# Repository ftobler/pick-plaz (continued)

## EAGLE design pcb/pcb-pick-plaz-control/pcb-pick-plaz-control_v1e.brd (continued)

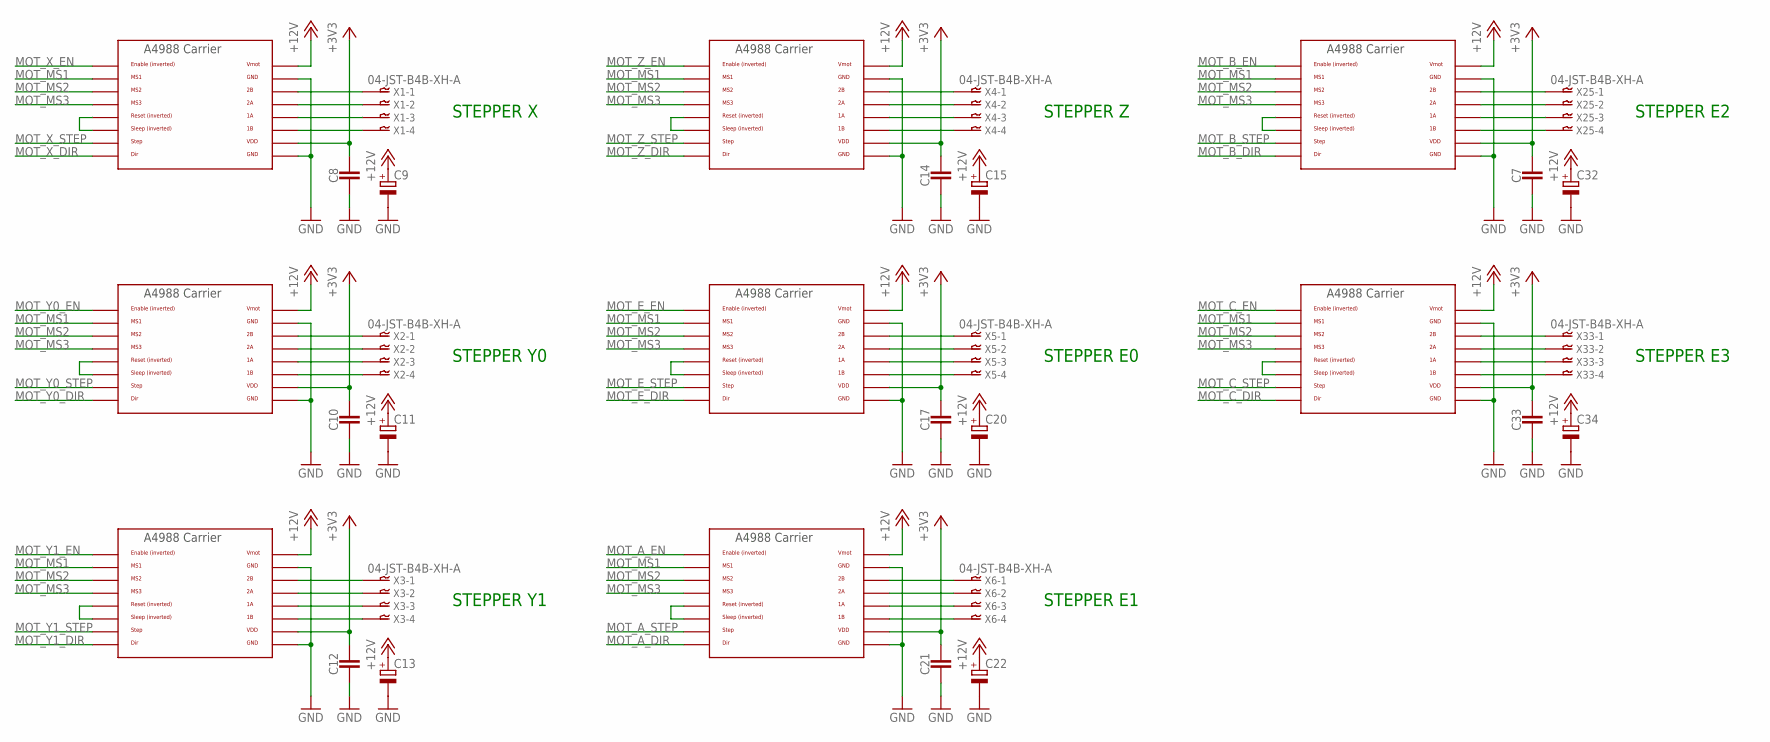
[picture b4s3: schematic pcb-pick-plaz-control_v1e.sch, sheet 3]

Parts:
C7, C8, C10, C12, C14, C17, C21, C33: CAPACITOR0603_CAP; 0603_CAP
C9, C11, C13, C15, C20, C22, C32, C34: CPOL-EU175TMP-0808; 175TMP-0808
U$2, U$3, U$4, U$5, U$6, U$7, U$8, U$9: A4988BREAKOUT
X1, X2, X3, X4, X5, X6, X25, X33: 04-JST-B4B-XH-A; B4B-XH

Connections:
+3V3: C7.1, C8.1, C10.1, C12.1, C14.1, C17.1, C21.1, C33.1, U$2.VDD, U$3.VDD, U$4.VDD, U$5.VDD, U$6.VDD, U$7.VDD, U$8.VDD, U$9.VDD; also elsewhere on the board
+12V: C9.+, C11.+, C13.+, C15.+, C20.+, C22.+, C32.+, C34.+, U$2.VMOT, U$3.VMOT, U$4.VMOT, U$5.VMOT, U$6.VMOT, U$7.VMOT, U$8.VMOT, U$9.VMOT; also elsewhere on the board
GND: C7.2, C8.2, C9.-, C10.2, C11.-, C12.2, C13.-, C14.2, C15.-, C17.2, C20.-, C21.2, C22.-, C32.-, C33.2, C34.-, U$2.GND, U$2.GND@0 (GND), U$3.GND, U$3.GND@0 (GND), U$4.GND, U$4.GND@0 (GND), U$5.GND, U$5.GND@0 (GND), U$6.GND, U$6.GND@0 (GND), U$7.GND, U$7.GND@0 (GND), U$8.GND, U$8.GND@0 (GND), U$9.GND, U$9.GND@0 (GND); also elsewhere on the board
MOT_A_DIR: U$7.DIR; also elsewhere on the board
MOT_A_EN: U$7.EN; also elsewhere on the board
MOT_A_STEP: U$7.STEP; also elsewhere on the board
MOT_B_DIR: U$8.DIR; also elsewhere on the board
MOT_B_EN: U$8.EN; also elsewhere on the board
MOT_B_STEP: U$8.STEP; also elsewhere on the board
MOT_C_DIR: U$9.DIR; also elsewhere on the board
MOT_C_EN: U$9.EN; also elsewhere on the board
MOT_C_STEP: U$9.STEP; also elsewhere on the board
MOT_E_DIR: U$6.DIR; also elsewhere on the board
MOT_E_EN: U$6.EN; also elsewhere on the board
MOT_E_STEP: U$6.STEP; also elsewhere on the board
MOT_MS1: U$2.MS1, U$3.MS1, U$4.MS1, U$5.MS1, U$6.MS1, U$7.MS1, U$8.MS1, U$9.MS1; also elsewhere on the board
MOT_MS2: U$2.MS2, U$3.MS2, U$4.MS2, U$5.MS2, U$6.MS2, U$7.MS2, U$8.MS2, U$9.MS2; also elsewhere on the board
MOT_MS3: U$2.MS3, U$3.MS3, U$4.MS3, U$5.MS3, U$6.MS3, U$7.MS3, U$8.MS3, U$9.MS3; also elsewhere on the board
MOT_X_DIR: U$2.DIR; also elsewhere on the board
MOT_X_EN: U$2.EN; also elsewhere on the board
MOT_X_STEP: U$2.STEP; also elsewhere on the board
MOT_Y0_DIR: U$3.DIR; also elsewhere on the board
MOT_Y0_EN: U$3.EN; also elsewhere on the board
MOT_Y0_STEP: U$3.STEP; also elsewhere on the board
MOT_Y1_DIR: U$4.DIR; also elsewhere on the board
MOT_Y1_EN: U$4.EN; also elsewhere on the board
MOT_Y1_STEP: U$4.STEP; also elsewhere on the board
MOT_Z_DIR: U$5.DIR; also elsewhere on the board
MOT_Z_EN: U$5.EN; also elsewhere on the board
MOT_Z_STEP: U$5.STEP; also elsewhere on the board
unnamed: U$2.2B, X1.P$1
unnamed: U$2.2A, X1.P$2
unnamed: U$2.1A, X1.P$3
unnamed: U$2.1B, X1.P$4
unnamed: U$6.2B, X5.P$1
unnamed: U$2.RST, U$2.SLP (SLEEP)
unnamed: U$6.2A, X5.P$2
unnamed: U$6.1A, X5.P$3
unnamed: U$3.2B, X2.P$1
unnamed: U$3.2A, X2.P$2
unnamed: U$3.1A, X2.P$3
unnamed: U$3.1B, X2.P$4
unnamed: U$3.RST, U$3.SLP (SLEEP)
unnamed: U$4.2B, X3.P$1
unnamed: U$4.2A, X3.P$2
unnamed: U$4.1A, X3.P$3
unnamed: U$4.1B, X3.P$4
unnamed: U$4.RST, U$4.SLP (SLEEP)
unnamed: U$5.2B, X4.P$1
unnamed: U$5.2A, X4.P$2
unnamed: U$5.1A, X4.P$3
unnamed: U$5.1B, X4.P$4
unnamed: U$5.RST, U$5.SLP (SLEEP)
unnamed: U$6.1B, X5.P$4
unnamed: U$6.RST, U$6.SLP (SLEEP)
unnamed: U$7.2B, X6.P$1
unnamed: U$7.2A, X6.P$2
unnamed: U$7.1A, X6.P$3
unnamed: U$7.1B, X6.P$4
unnamed: U$7.RST, U$7.SLP (SLEEP)
unnamed: U$8.2B, X25.P$1
unnamed: U$8.2A, X25.P$2
unnamed: U$8.1A, X25.P$3
unnamed: U$8.1B, X25.P$4
unnamed: U$8.RST, U$8.SLP (SLEEP)
unnamed: U$9.2B, X33.P$1
unnamed: U$9.2A, X33.P$2
unnamed: U$9.1A, X33.P$3
unnamed: U$9.1B, X33.P$4
unnamed: U$9.RST, U$9.SLP (SLEEP)

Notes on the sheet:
STEPPER X
STEPPER Y0
STEPPER Y1
STEPPER Z
STEPPER E0
STEPPER E1
STEPPER E2
STEPPER E3

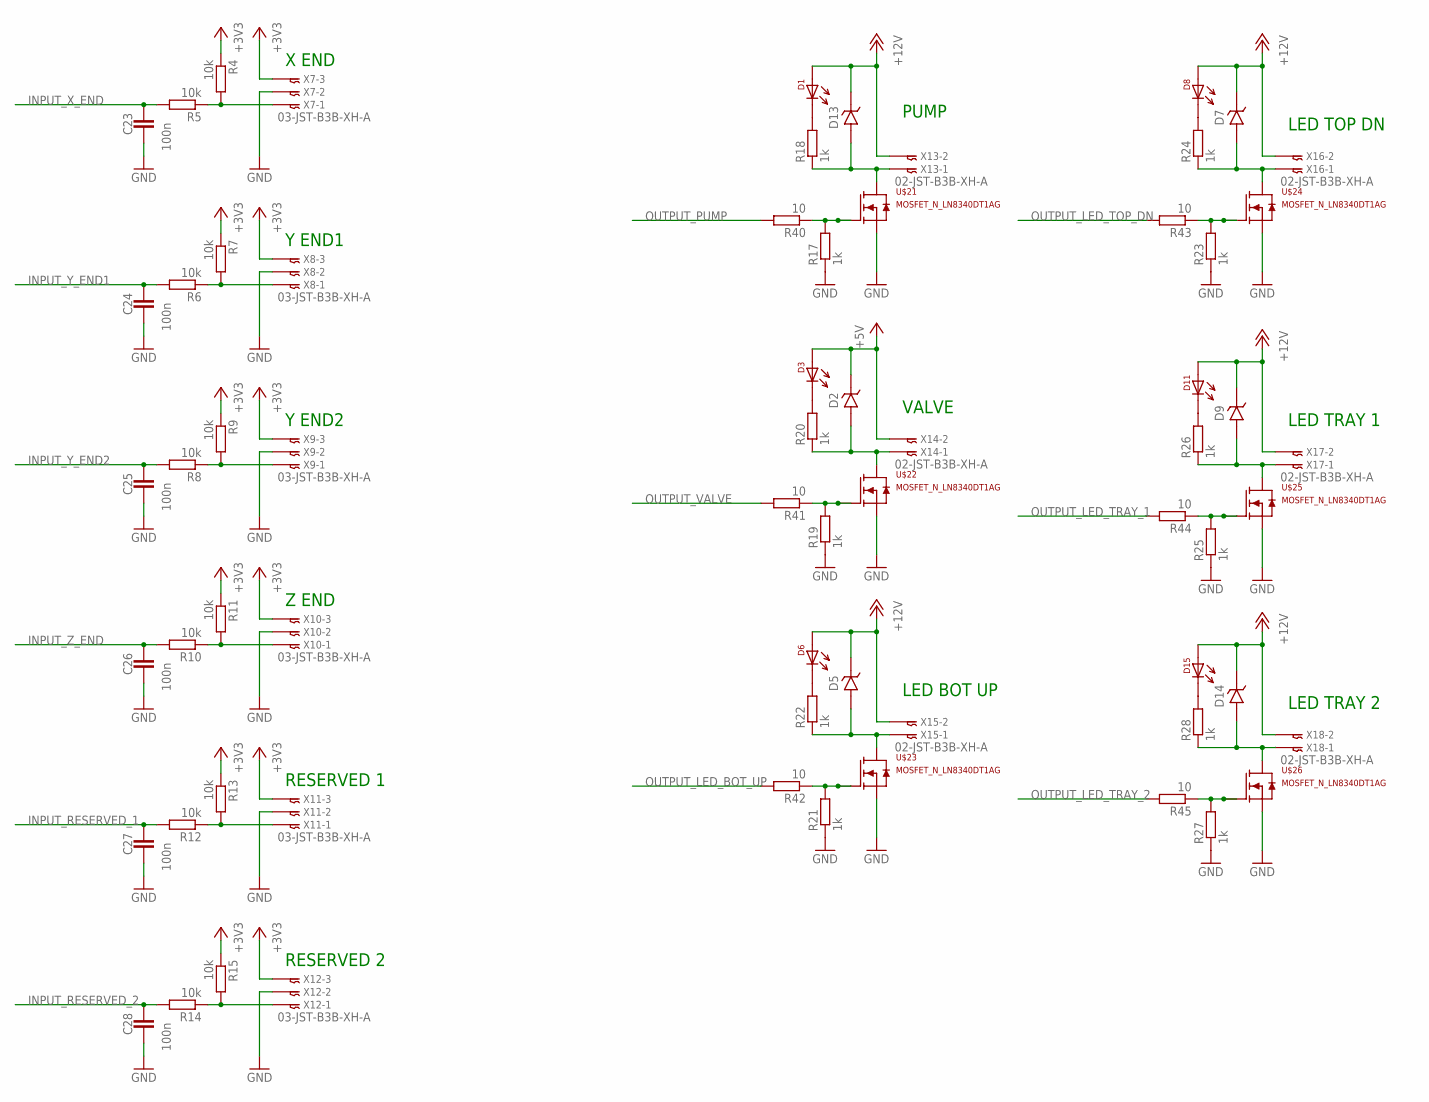
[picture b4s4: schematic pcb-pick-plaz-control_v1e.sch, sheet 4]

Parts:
C23, C24, C25, C26, C27, C28: 100n; 0603_CAP
D1, D3, D6, D8, D11, D15: LED-0805; 0805-DOT
D2, D5, D7, D9, D13, D14: DIODE_ZENERSOD123; SOD123
R4, R5, R6, R7, R8, R9, R10, R11, R12, R13, R14, R15: 10k; 0603-RES
R17, R18, R19, R20, R21, R22, R23, R24, R25, R26, R27, R28: 1k; 0603-RES
R40, R41, R42, R43, R44, R45: 10; 0603-RES
U$21, U$22, U$23, U$24, U$25, U$26: MOSFET_N_LN8340DT1AG; DFN3030-8B
X7, X8, X9, X10, X11, X12: 03-JST-B3B-XH-A; B3B-XH
X13, X14, X15, X16, X17, X18: 02-JST-B3B-XH-A; B2B-XH

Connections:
+3V3: R4.1, R7.1, R9.1, R11.1, R13.1, R15.1, X7.P$3, X8.P$3, X9.P$3, X10.P$3, X11.P$3, X12.P$3; also elsewhere on the board
+5V: D2.K (CATHODE), D3.1, X14.P$2; also elsewhere on the board
+12V: D1.1, D5.K (CATHODE), D6.1, D7.K (CATHODE), D8.1, D9.K (CATHODE), D11.1, D13.K (CATHODE), D14.K (CATHODE), D15.1, X13.P$2, X15.P$2, X16.P$2, X17.P$2, X18.P$2; also elsewhere on the board
GND: C23.2, C24.2, C25.2, C26.2, C27.2, C28.2, R17.1, R19.1, R21.1, R23.1, R25.1, R27.1, U$21.S1 (S), U$21.S2 (S), U$21.S3 (S), U$22.S1 (S), U$22.S2 (S), U$22.S3 (S), U$23.S1 (S), U$23.S2 (S), U$23.S3 (S), U$24.S1 (S), U$24.S2 (S), U$24.S3 (S), U$25.S1 (S), U$25.S2 (S), U$25.S3 (S), U$26.S1 (S), U$26.S2 (S), U$26.S3 (S), X7.P$2, X8.P$2, X9.P$2, X10.P$2, X11.P$2, X12.P$2; also elsewhere on the board
INPUT_RESERVED_1: C27.1, R12.2; also elsewhere on the board
INPUT_RESERVED_2: C28.1, R14.2; also elsewhere on the board
INPUT_X_END: C23.1, R5.2; also elsewhere on the board
INPUT_Y_END1: C24.1, R6.2; also elsewhere on the board
INPUT_Y_END2: C25.1, R8.2; also elsewhere on the board
INPUT_Z_END: C26.1, R10.2; also elsewhere on the board
unnamed: R4.2, R5.1, X7.P$1
unnamed: R6.1, R7.2, X8.P$1
unnamed: R8.1, R9.2, X9.P$1
unnamed: R10.1, R11.2, X10.P$1
unnamed: R12.1, R13.2, X11.P$1
unnamed: R14.1, R15.2, X12.P$1
unnamed: D13.A (ANODE), R18.1, U$21.D, X13.P$1
unnamed: R17.2, R40.1, U$21.G
unnamed: D1.2, R18.2
unnamed: D2.A (ANODE), R20.1, U$22.D, X14.P$1
unnamed: R19.2, R41.1, U$22.G
unnamed: D3.2, R20.2
unnamed: D5.A (ANODE), R22.1, U$23.D, X15.P$1
unnamed: R21.2, R42.1, U$23.G
unnamed: D6.2, R22.2
unnamed: D7.A (ANODE), R24.1, U$24.D, X16.P$1
unnamed: R23.2, R43.1, U$24.G
unnamed: D8.2, R24.2
unnamed: D9.A (ANODE), R26.1, U$25.D, X17.P$1
unnamed: R25.2, R44.1, U$25.G
unnamed: D11.2, R26.2
unnamed: D14.A (ANODE), R28.1, U$26.D, X18.P$1
unnamed: R27.2, R45.1, U$26.G
unnamed: D15.2, R28.2
OUTPUT_LED_BOT_UP: R42.2; also elsewhere on the board
OUTPUT_LED_TOP_DN: R43.2; also elsewhere on the board
OUTPUT_LED_TRAY_1: R44.2; also elsewhere on the board
OUTPUT_LED_TRAY_2: R45.2; also elsewhere on the board
OUTPUT_PUMP: R40.2; also elsewhere on the board
OUTPUT_VALVE: R41.2; also elsewhere on the board

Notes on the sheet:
PUMP
VALVE
LED BOT UP
LED TOP DN
LED TRAY 1
LED TRAY 2
X END
Y END1
Y END2
Z END
RESERVED 1
RESERVED 2

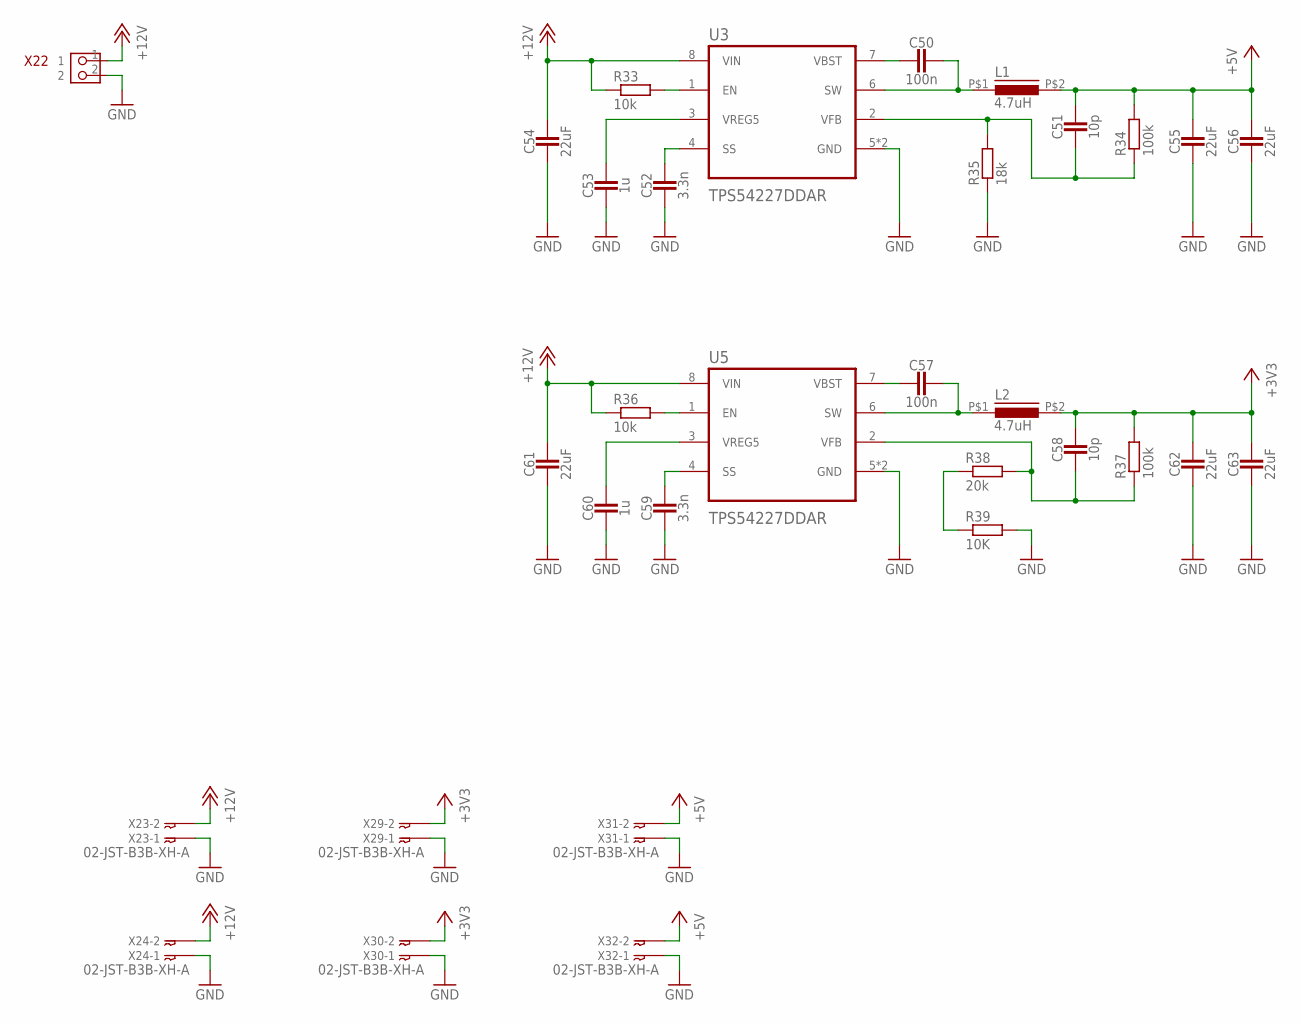
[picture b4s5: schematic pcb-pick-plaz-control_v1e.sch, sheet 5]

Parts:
C50, C57: 100n; 0603_CAP
C51, C58: 10p; 0603_CAP
C52, C59: 3.3n; 0603_CAP
C53, C60: 1u; 0603_CAP
C54, C61: 22uF; 1206_CAP
C55, C56, C62, C63: 22uF; 0805_CAP
L1, L2: 4.7uH; IND_CR4
R33, R36: 10k; 0603-RES
R34, R37: 100k; 0603-RES
R35: 18k; 0603-RES
R38: 20k; 0603-RES
R39: 10K; 0603-RES
U3, U5: TPS54227DDAR; TPS54227DDAR_VREG_LM5017MR/NOPB
X22: PIN_2X13.81MM_LONGPAD; PIN_2X1_3.81MM_LONGPAD
X23, X24, X29, X30, X31, X32: 02-JST-B3B-XH-A; B2B-XH

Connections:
+3V3: C58.1, C62.P$1 (1), C63.P$1 (1), L2.P$2 (2), R37.2, X29.P$2, X30.P$2; also elsewhere on the board
+5V: C51.1, C55.P$1 (1), C56.P$1 (1), L1.P$2 (2), R34.2, X31.P$2, X32.P$2; also elsewhere on the board
+12V: C54.1, C61.1, R33.1, R36.1, U3.8 (VIN), U5.8 (VIN), X22.1, X23.P$2, X24.P$2; also elsewhere on the board
GND: C52.2, C53.2, C54.2, C55.P$2 (2), C56.P$2 (2), C59.2, C60.2, C61.2, C62.P$2 (2), C63.P$2 (2), R35.1, R39.2, U3.5 (GND), U3.9 (GND), U5.5 (GND), U5.9 (GND), X22.2, X23.P$1, X24.P$1, X29.P$1, X30.P$1, X31.P$1, X32.P$1; also elsewhere on the board
unnamed: C50.2, U3.7 (VBST)
unnamed: C50.1, L1.P$1 (1), U3.6 (SW)
unnamed: C51.2, R34.1, R35.2, U3.2 (VFB)
unnamed: C52.1, U3.4 (SS)
unnamed: C53.1, U3.3 (VREG5)
unnamed: R33.2, U3.1 (EN)
unnamed: C57.2, U5.7 (VBST)
unnamed: C57.1, L2.P$1 (1), U5.6 (SW)
unnamed: C58.2, R37.1, R38.2, U5.2 (VFB)
unnamed: C59.1, U5.4 (SS)
unnamed: C60.1, U5.3 (VREG5)
unnamed: R36.2, U5.1 (EN)
unnamed: R38.1, R39.1

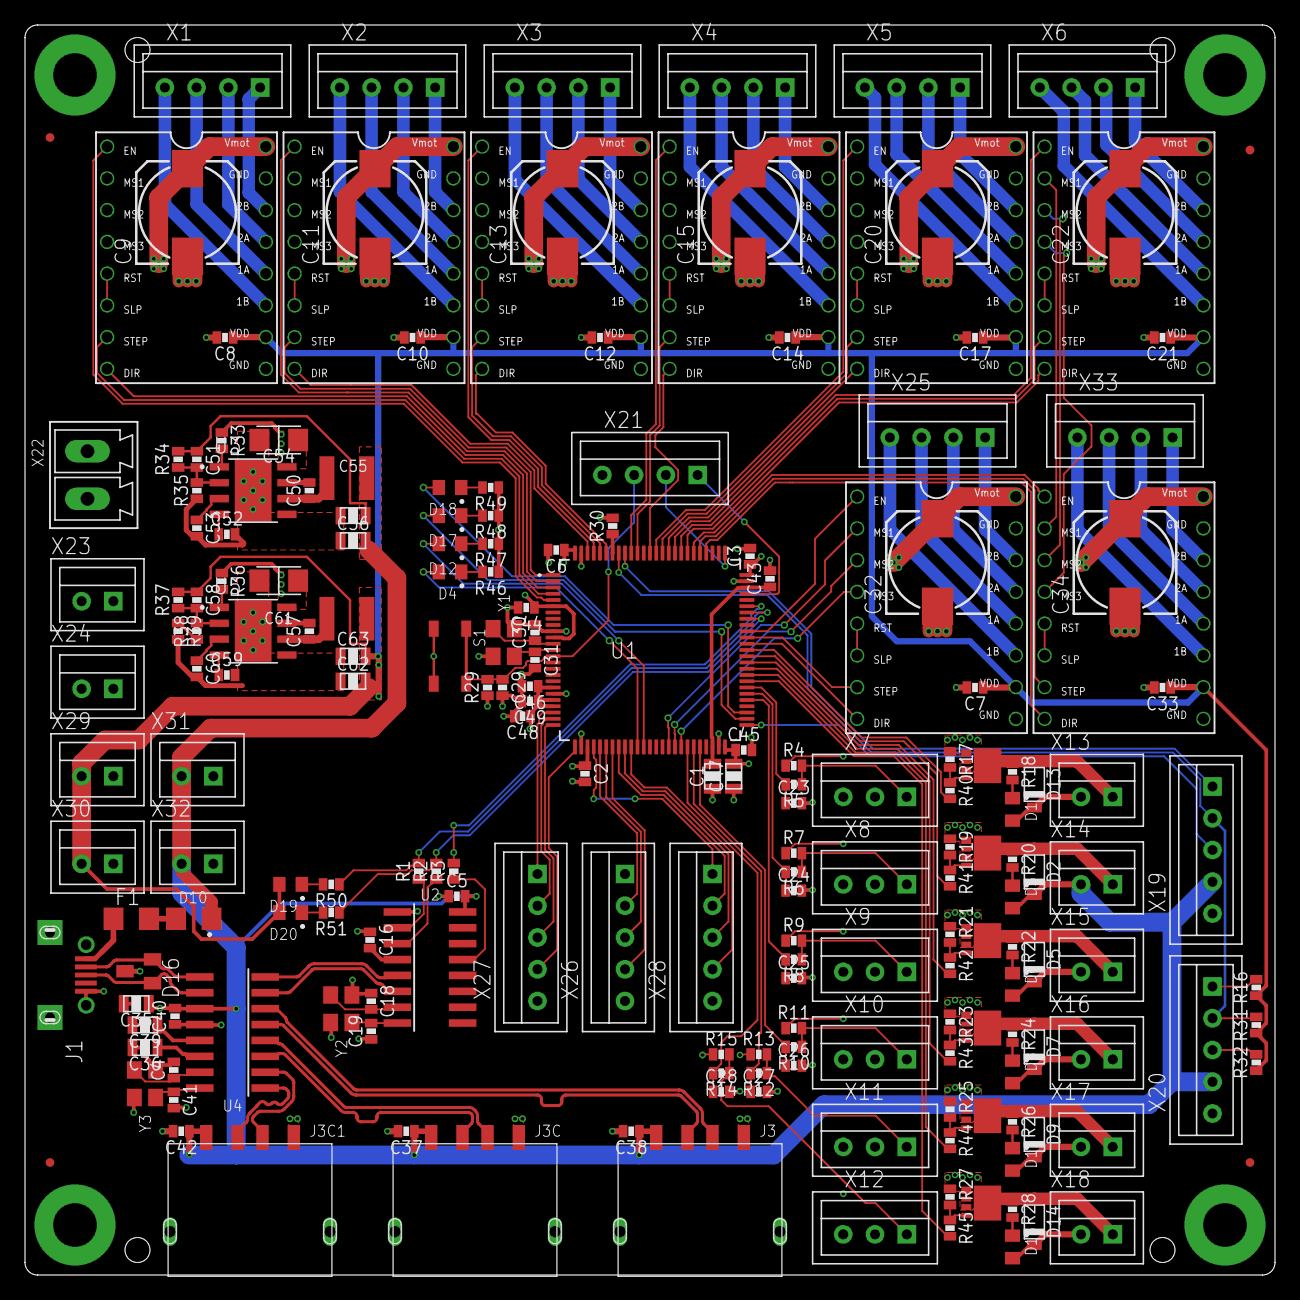
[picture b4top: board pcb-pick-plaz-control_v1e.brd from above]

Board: 4 copper layers, 100.0 x 100.0 mm, 202 parts (0 on the bottom side), 176 nets.

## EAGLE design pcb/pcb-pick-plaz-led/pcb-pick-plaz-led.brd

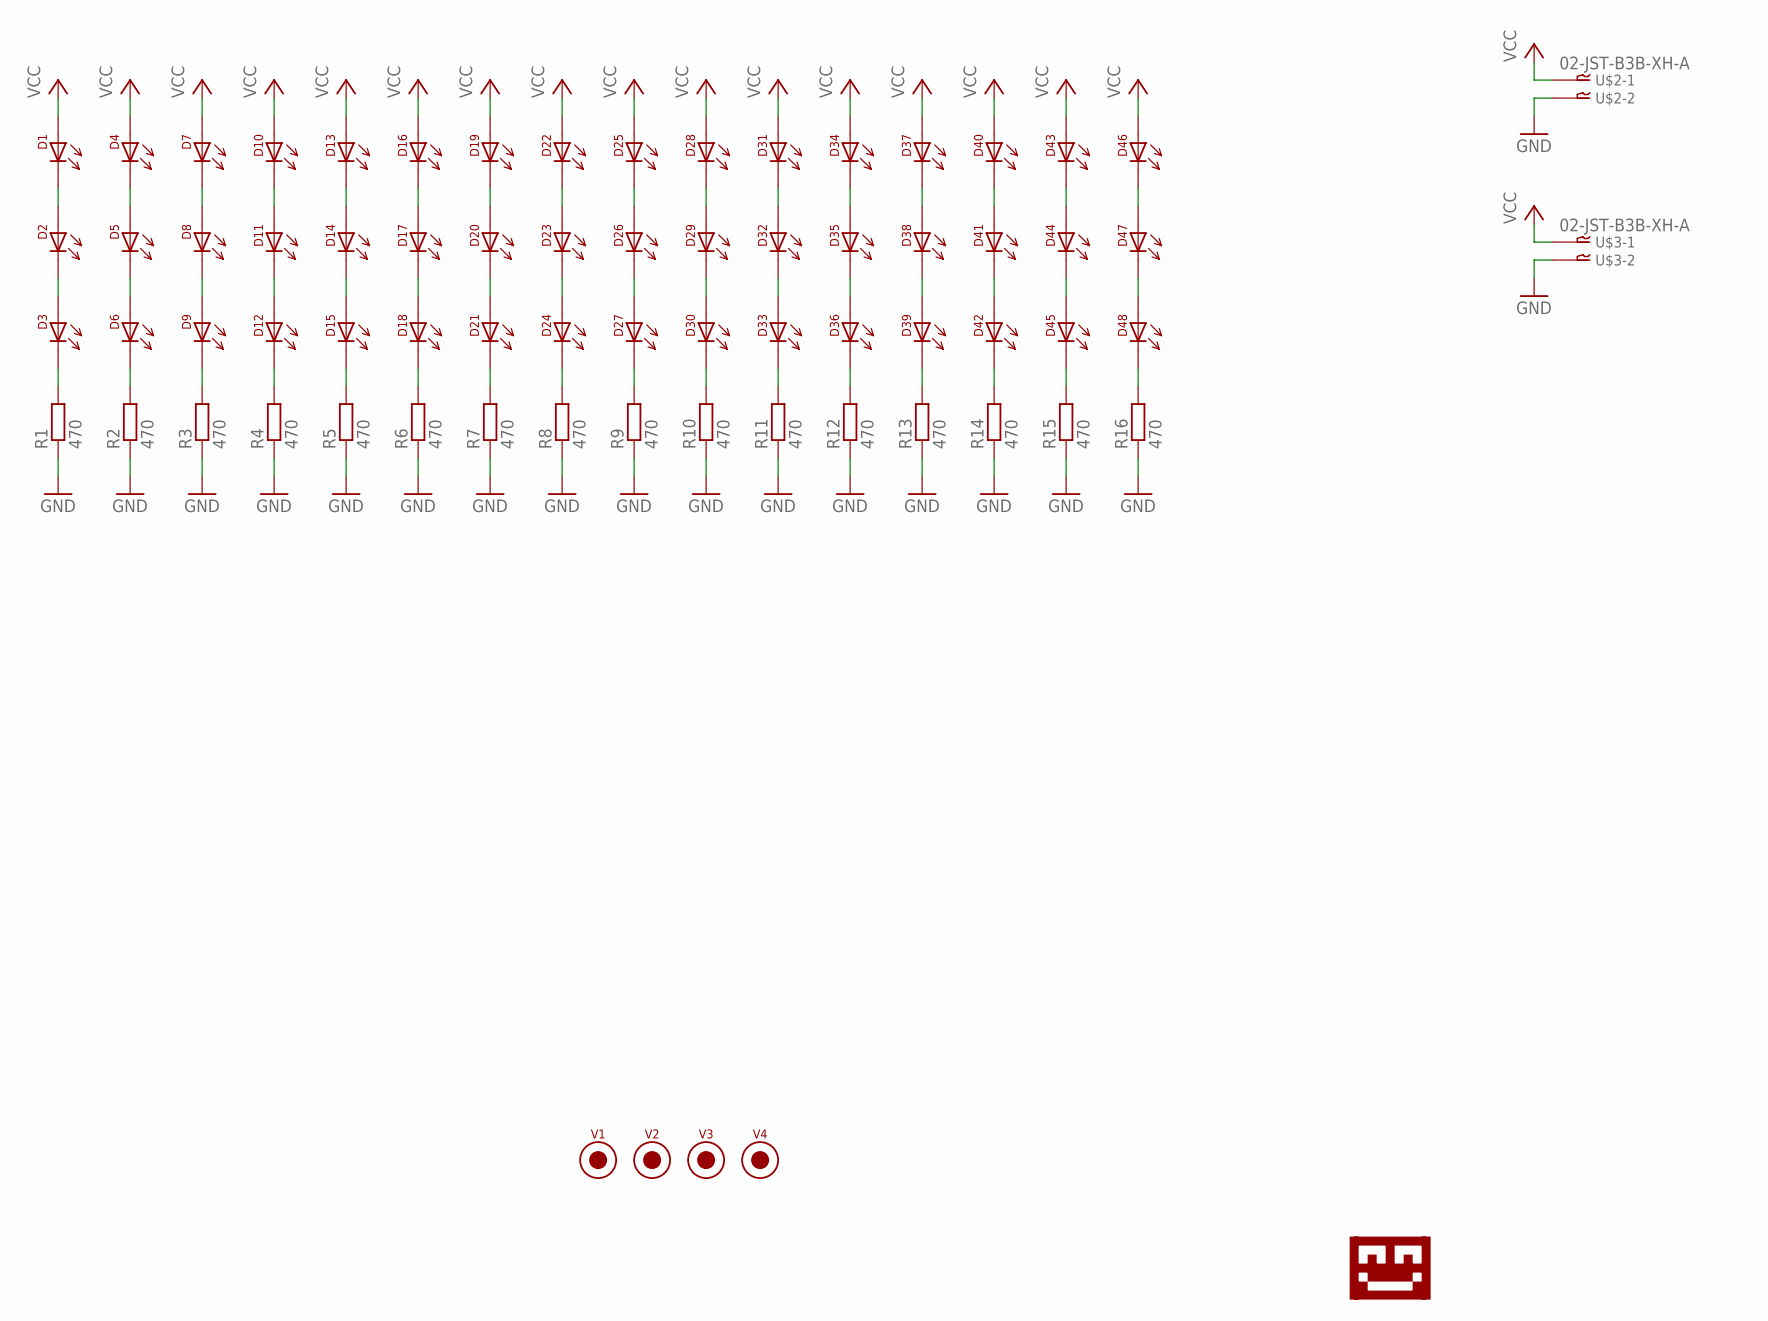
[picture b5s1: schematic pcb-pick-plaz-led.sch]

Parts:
D1, D2, D3, D4, D5, D6, D7, D8, D9, D10, D11, D12, D13, D14, D15, D16, D17, D18, D19, D20, D21, D22, D23, D24, D25, D26, D27, D28, D29, D30, D31, D32, D33, D34, D35, D36, D37, D38, D39, D40, D41, D42, D43, D44, D45, D46, D47, D48: LED-5730; 5730-LED
R1, R2, R3, R4, R5, R6, R7, R8, R9, R10, R11, R12, R13, R14, R15, R16: 470; 0805_RES
U$1: LOGO-TOBENG-1MM-FINISH; TOBENG-1MM-FINISH
U$2, U$3: 02-JST-B3B-XH-A; B2B-XH
V1, V2, V3, V4: FIDUCIAL2MM; FIDUCIAL_2MM

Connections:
GND: R1.1, R2.1, R3.1, R4.1, R5.1, R6.1, R7.1, R8.1, R9.1, R10.1, R11.1, R12.1, R13.1, R14.1, R15.1, R16.1, U$2.P$2, U$3.P$2
unnamed: D1.C (2), D2.A1 (1), D2.A2 (1)
unnamed: D2.C (2), D3.A1 (1), D3.A2 (1)
unnamed: D3.C (2), R1.2
unnamed: D4.C (2), D5.A1 (1), D5.A2 (1)
unnamed: D5.C (2), D6.A1 (1), D6.A2 (1)
unnamed: D6.C (2), R2.2
unnamed: D7.C (2), D8.A1 (1), D8.A2 (1)
unnamed: D8.C (2), D9.A1 (1), D9.A2 (1)
unnamed: D9.C (2), R3.2
unnamed: D10.C (2), D11.A1 (1), D11.A2 (1)
unnamed: D11.C (2), D12.A1 (1), D12.A2 (1)
unnamed: D12.C (2), R4.2
unnamed: D13.C (2), D14.A1 (1), D14.A2 (1)
unnamed: D14.C (2), D15.A1 (1), D15.A2 (1)
unnamed: D15.C (2), R5.2
unnamed: D16.C (2), D17.A1 (1), D17.A2 (1)
unnamed: D17.C (2), D18.A1 (1), D18.A2 (1)
unnamed: D18.C (2), R6.2
unnamed: D19.C (2), D20.A1 (1), D20.A2 (1)
unnamed: D20.C (2), D21.A1 (1), D21.A2 (1)
unnamed: D21.C (2), R7.2
unnamed: D22.C (2), D23.A1 (1), D23.A2 (1)
unnamed: D23.C (2), D24.A1 (1), D24.A2 (1)
unnamed: D24.C (2), R8.2
unnamed: D25.C (2), D26.A1 (1), D26.A2 (1)
unnamed: D26.C (2), D27.A1 (1), D27.A2 (1)
unnamed: D27.C (2), R9.2
unnamed: D28.C (2), D29.A1 (1), D29.A2 (1)
unnamed: D29.C (2), D30.A1 (1), D30.A2 (1)
unnamed: D30.C (2), R10.2
unnamed: D31.C (2), D32.A1 (1), D32.A2 (1)
unnamed: D32.C (2), D33.A1 (1), D33.A2 (1)
unnamed: D33.C (2), R11.2
unnamed: D34.C (2), D35.A1 (1), D35.A2 (1)
unnamed: D35.C (2), D36.A1 (1), D36.A2 (1)
unnamed: D36.C (2), R12.2
unnamed: D37.C (2), D38.A1 (1), D38.A2 (1)
unnamed: D38.C (2), D39.A1 (1), D39.A2 (1)
unnamed: D39.C (2), R13.2
unnamed: D40.C (2), D41.A1 (1), D41.A2 (1)
unnamed: D41.C (2), D42.A1 (1), D42.A2 (1)
unnamed: D42.C (2), R14.2
unnamed: D43.C (2), D44.A1 (1), D44.A2 (1)
unnamed: D44.C (2), D45.A1 (1), D45.A2 (1)
unnamed: D45.C (2), R15.2
unnamed: D46.C (2), D47.A1 (1), D47.A2 (1)
unnamed: D47.C (2), D48.A1 (1), D48.A2 (1)
unnamed: D48.C (2), R16.2
VCC: D1.A1 (1), D1.A2 (1), D4.A1 (1), D4.A2 (1), D7.A1 (1), D7.A2 (1), D10.A1 (1), D10.A2 (1), D13.A1 (1), D13.A2 (1), D16.A1 (1), D16.A2 (1), D19.A1 (1), D19.A2 (1), D22.A1 (1), D22.A2 (1), D25.A1 (1), D25.A2 (1), D28.A1 (1), D28.A2 (1), D31.A1 (1), D31.A2 (1), D34.A1 (1), D34.A2 (1), D37.A1 (1), D37.A2 (1), D40.A1 (1), D40.A2 (1), D43.A1 (1), D43.A2 (1), D46.A1 (1), D46.A2 (1), U$2.P$1, U$3.P$1

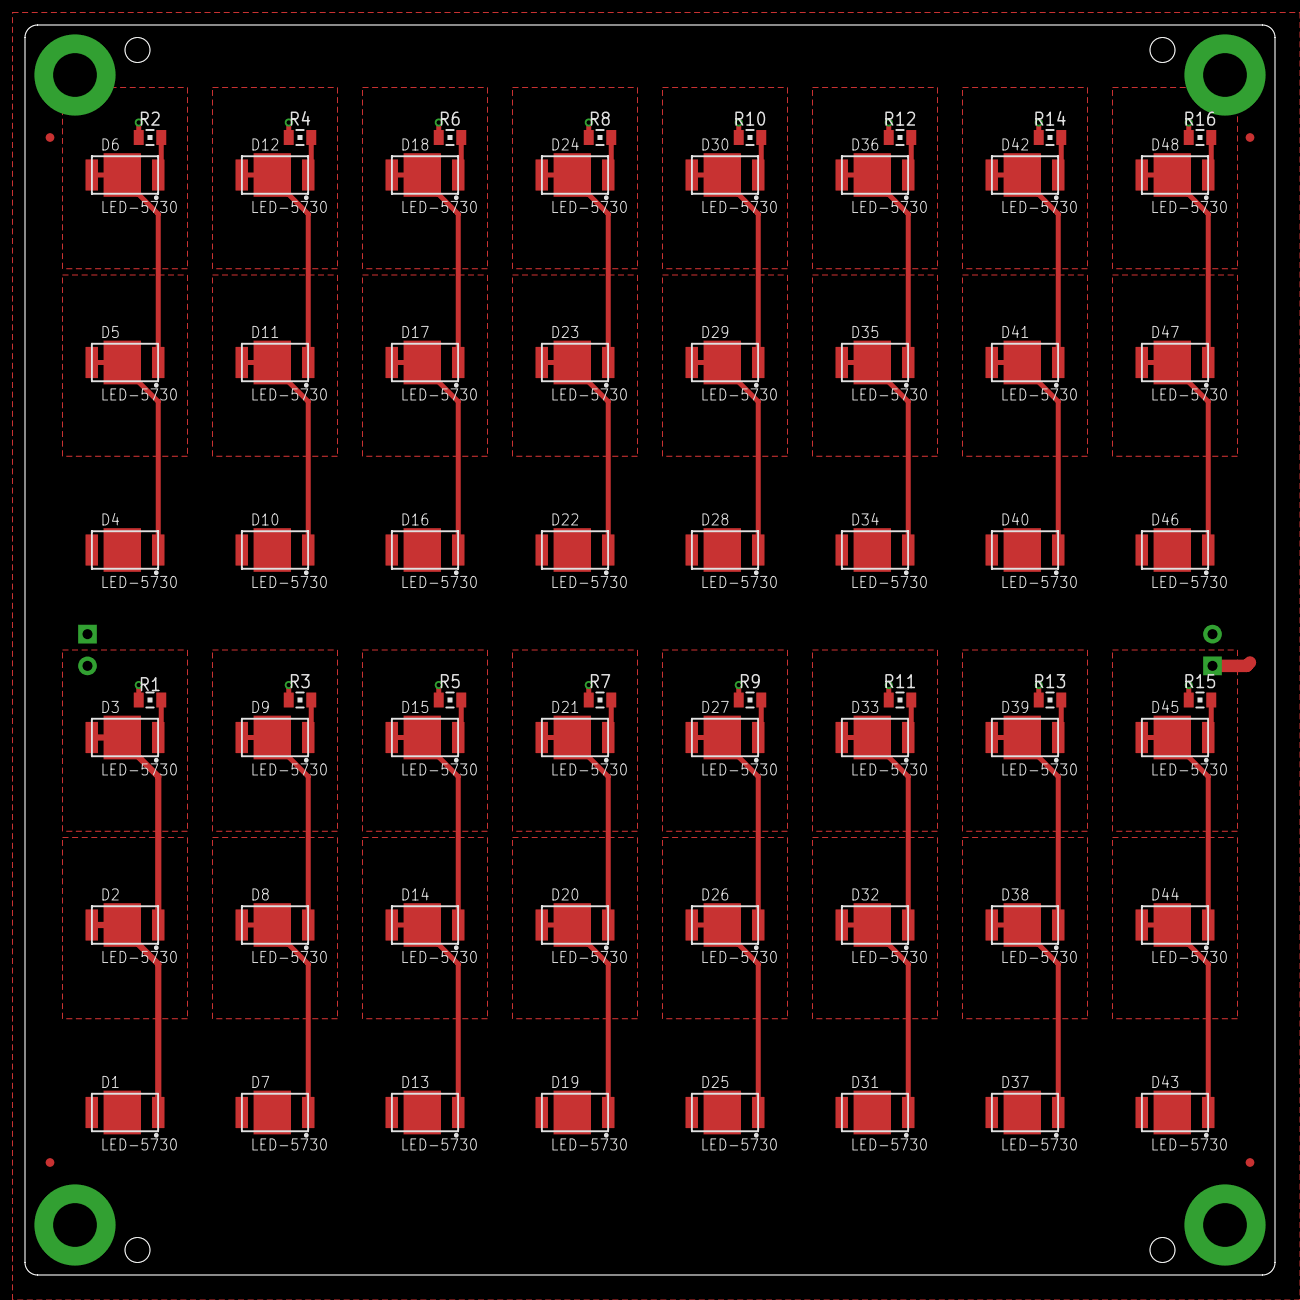
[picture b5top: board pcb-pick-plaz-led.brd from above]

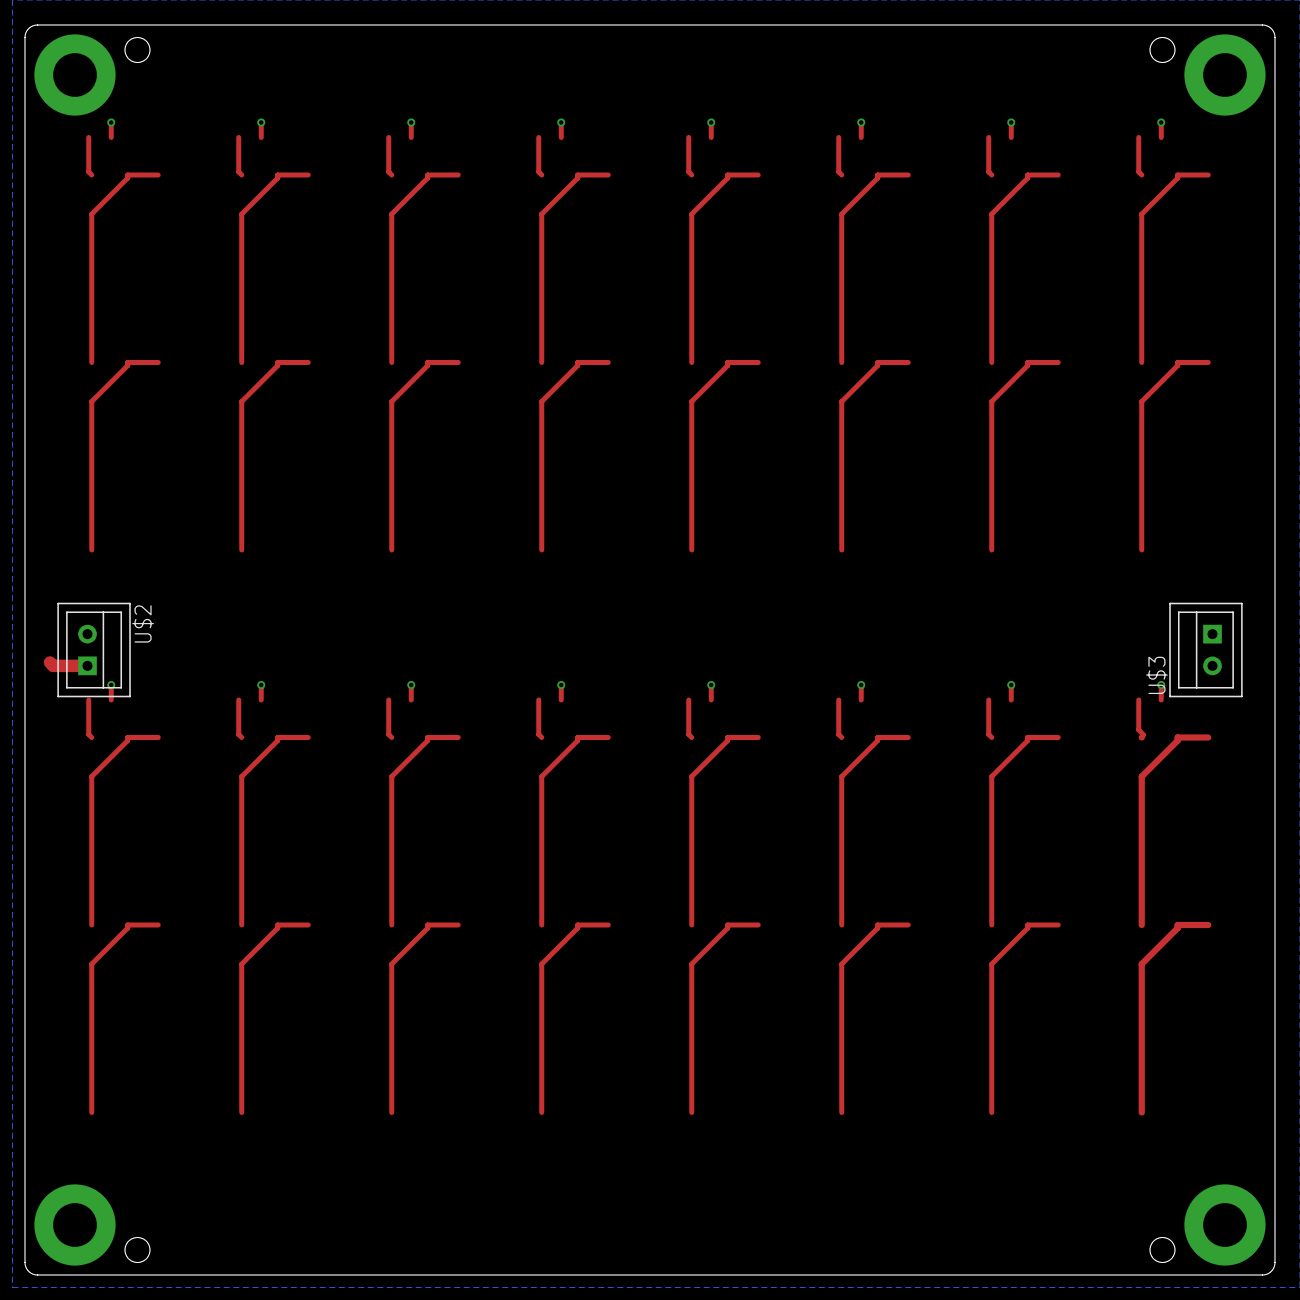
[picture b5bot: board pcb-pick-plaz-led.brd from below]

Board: 2 copper layers, 100.0 x 100.0 mm, 71 parts (2 on the bottom side), 50 nets.

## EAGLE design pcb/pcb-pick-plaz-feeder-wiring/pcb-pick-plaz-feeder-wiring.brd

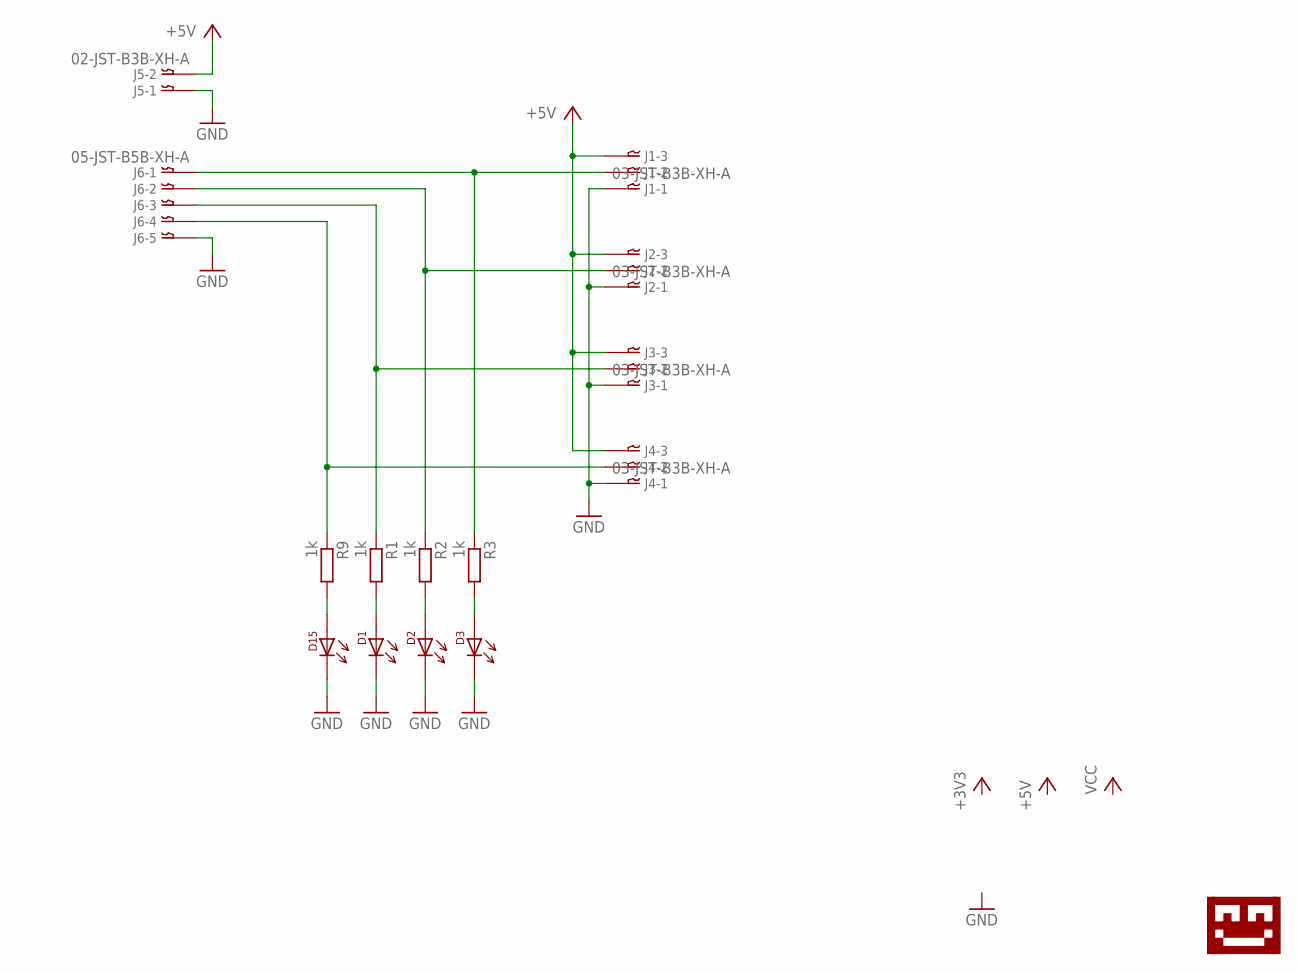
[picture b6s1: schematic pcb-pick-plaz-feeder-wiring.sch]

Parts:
D1, D2, D3, D15: LED-0805; 0805-DOT
J1, J2, J3, J4: 03-JST-B3B-XH-A; B3B-XH
J5: 02-JST-B3B-XH-A; B2B-XH
J6: 05-JST-B5B-XH-A; B5B-XH
R1, R2, R3, R9: 1k; 0603-RES
U$1: LOGO-TOBENG-1MM-FINISH; TOBENG-1MM-FINISH

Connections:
+5V: J1.P$3, J2.P$3, J3.P$3, J4.P$3, J5.P$2
GND: D1.2, D2.2, D3.2, D15.2, J1.P$1, J2.P$1, J3.P$1, J4.P$1, J5.P$1, J6.P$5
unnamed: J3.P$2, J6.P$3, R1.1
unnamed: J4.P$2, J6.P$4, R9.1
unnamed: D1.1, R1.2
unnamed: J2.P$2, J6.P$2, R2.1
unnamed: J1.P$2, J6.P$1, R3.1
unnamed: D15.1, R9.2
unnamed: D2.1, R2.2
unnamed: D3.1, R3.2

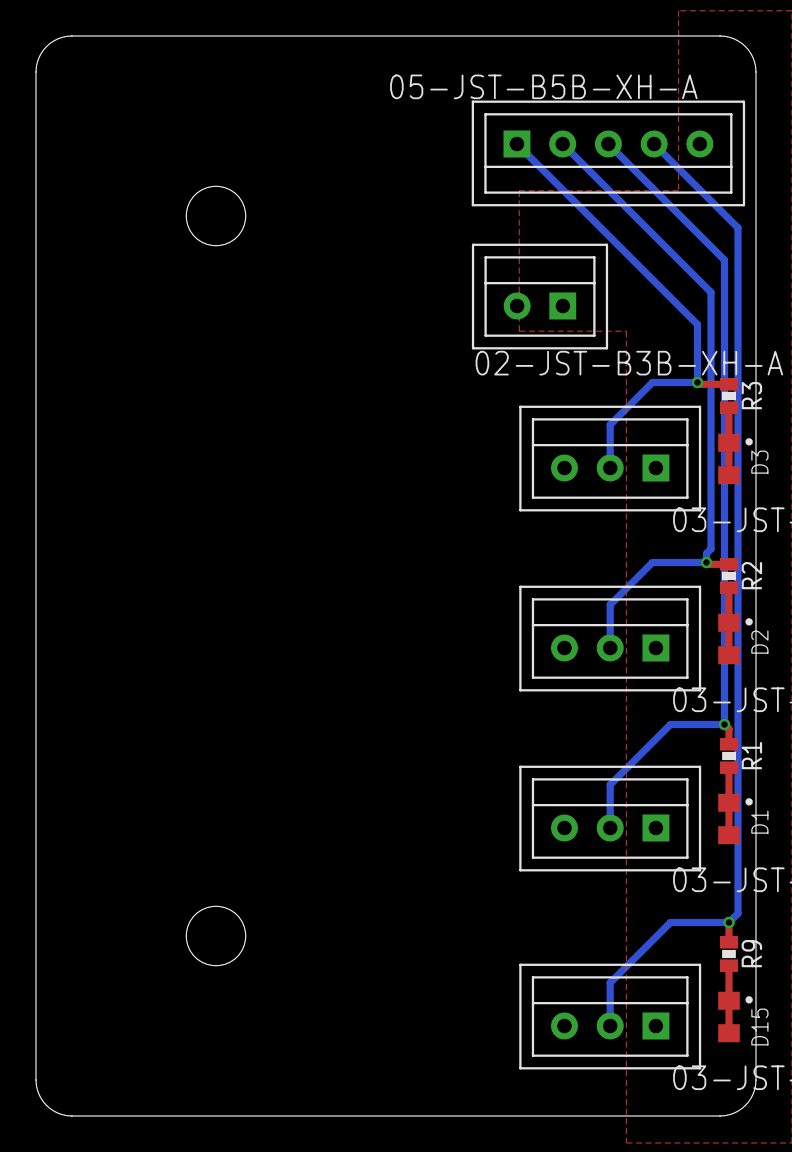
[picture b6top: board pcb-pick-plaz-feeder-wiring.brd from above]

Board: 2 copper layers, 40.0 x 60.0 mm, 15 parts (0 on the bottom side), 10 nets.

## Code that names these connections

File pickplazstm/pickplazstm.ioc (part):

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PA6.Mode=Full_Duplex_Master
Mcu.UserName=STM32F411VETx
PC12.Signal=GPIO_Output
PB13.Signal=GPIO_Output
RCC.SYSCLKSource=RCC_SYSCLKSOURCE_PLLCLK
PD13.Signal=GPIO_Output
PH0\ -\ OSC_IN.Signal=RCC_OSC_IN
PD4.Signal=GPIO_Output
PB6.Signal=I2C1_SCL
PC7.Signal=GPIO_Output
PB6.Mode=I2C
PD0.Signal=GPIO_Output
PD8.Signal=GPIO_Input
PE5.Signal=GPIO_Output
PE1.Signal=GPIO_Output
RCC.HSE_VALUE=16000000
PB2.Signal=GPIO_Output
PE13.Signal=GPIO_Input
PA14.Mode=Serial_Wire
PE2.Signal=GPIO_Output
PB7.Signal=I2C1_SDA
PE10.Signal=GPIO_Output
PE4.Signal=GPIO_Output
Mcu.Package=LQFP100
PB9.Signal=GPIO_Output
PB1.Signal=GPIO_Output
PA6.Signal=SPI1_MISO
PD12.Signal=GPIO_Output
PA10.Signal=USART1_RX
PC5.Signal=GPIO_Output
PD6.Signal=GPIO_Output
PD15.Signal=GPIO_Output
PB4.Signal=GPIO_Output
PA3.Signal=ADCx_IN3
PA5.Mode=Full_Duplex_Master
PA7.Mode=Full_Duplex_Master
PA10.Mode=Asynchronous
PC11.Signal=GPIO_Output
PD3.Signal=GPIO_Output
PH1\ -\ OSC_OUT.Mode=HSE-External-Oscillator
PC8.Signal=GPIO_Output
PC4.Signal=GPIO_Output
PC6.Signal=GPIO_Output
PD7.Signal=GPIO_Output
PD1.Signal=GPIO_Output
PD9.Signal=GPIO_Input
PD5.Signal=GPIO_Output
PA0-WKUP.Signal=ADCx_IN0
PD10.Signal=GPIO_Input
PA13.Signal=SYS_JTMS-SWDIO
PA9.Mode=Asynchronous
PH0\ -\ OSC_IN.Mode=HSE-External-Oscillator
PA9.Signal=USART1_TX
PE11.Signal=GPIO_Output
PA1.Signal=ADCx_IN1
PB14.Signal=GPIO_Output
PA5.Signal=SPI1_SCK
PH1\ -\ OSC_OUT.Signal=RCC_OSC_OUT
board=custom
PE14.Signal=GPIO_Input
PE15.Signal=GPIO_Input
PE6.Signal=GPIO_Output
PA13.Mode=Serial_Wire
Mcu.Name=STM32F411V(C-E)Tx
PE0.Signal=GPIO_Output
PE12.Signal=GPIO_Output
PA2.Signal=ADCx_IN2
PD14.Signal=GPIO_Output
PA4.Signal=GPIO_Output
RCC.SYSCLKFreq_VALUE=100000000
PB5.Signal=GPIO_Output
PD11.Signal=GPIO_Output
PA11.Signal=GPIO_Input
PB7.Mode=I2C
PA14.Signal=SYS_JTCK-SWCLK
PE3.Signal=GPIO_Output
PB8.Signal=GPIO_Output
PC9.Signal=GPIO_Output
PD2.Signal=GPIO_Output
PB0.Signal=GPIO_Output
PB12.Signal=GPIO_Input
PA7.Signal=SPI1_MOSI

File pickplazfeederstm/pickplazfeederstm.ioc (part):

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Mcu.Name=STM32F030C8Tx
Mcu.Package=LQFP48
Mcu.UserName=STM32F030C8Tx
PA10.GPIOParameters=GPIO_Label
PA10.GPIO_Label=LED1
PA10.Signal=S_TIM1_CH3
PA11.GPIOParameters=GPIO_Label
PA11.GPIO_Label=LED0
PA11.Signal=S_TIM1_CH4
PA13.Mode=Serial_Wire
PA13.Signal=SYS_SWDIO
PA14.Mode=Serial_Wire
PA14.Signal=SYS_SWCLK
PA3.GPIOParameters=GPIO_Label
PA3.GPIO_Label=FEED
PA3.Signal=GPIO_Input
PA4.GPIOParameters=GPIO_Label
PA4.GPIO_Label=OPTO_INTERRUPT
PA4.Mode=IN4
PA4.Signal=ADC_IN4
PA5.GPIOParameters=GPIO_Label
PA5.GPIO_Label=OPTO_LED
PA5.Signal=GPIO_Output
PA6.GPIOParameters=GPIO_Label
PA6.GPIO_Label=MOT_NEG
PA6.Signal=S_TIM3_CH1
PA7.GPIOParameters=GPIO_Label
PA7.GPIO_Label=MOT_POS
PA7.Signal=S_TIM3_CH2
PA8.GPIOParameters=GPIO_Label
PA8.GPIO_Label=LED3
PA8.Signal=S_TIM1_CH1
PA9.GPIOParameters=GPIO_Label
PA9.GPIO_Label=LED2
PA9.Signal=S_TIM1_CH2
PB10.GPIOParameters=GPIO_Label
PB10.GPIO_Label=SW_BACKWARD
PB10.Signal=GPIO_Input
PB11.GPIOParameters=GPIO_Label
PB11.GPIO_Label=LED4
PB11.Signal=GPIO_Output
PB2.GPIOParameters=GPIO_Label
PB2.GPIO_Label=SW_FORWARD
PB2.Signal=GPIO_Input
PB3.GPIOParameters=GPIO_Label
PB3.GPIO_Label=TP1
PB3.Signal=GPIO_Output
PB4.GPIOParameters=GPIO_Label
PB4.GPIO_Label=TP2
PB4.Signal=GPIO_Output
PB5.GPIOParameters=GPIO_Label
PB5.GPIO_Label=TP3
PB5.Signal=GPIO_Output
PB6.GPIOParameters=GPIO_Label
PB6.GPIO_Label=TP4
PB6.Signal=GPIO_Output
PB7.GPIOParameters=GPIO_Label
PB7.GPIO_Label=TP5
PB7.Signal=GPIO_Output
RCC.SYSCLKFreq_VALUE=48000000
RCC.SYSCLKSource=RCC_SYSCLKSOURCE_PLLCLK
board=custom
